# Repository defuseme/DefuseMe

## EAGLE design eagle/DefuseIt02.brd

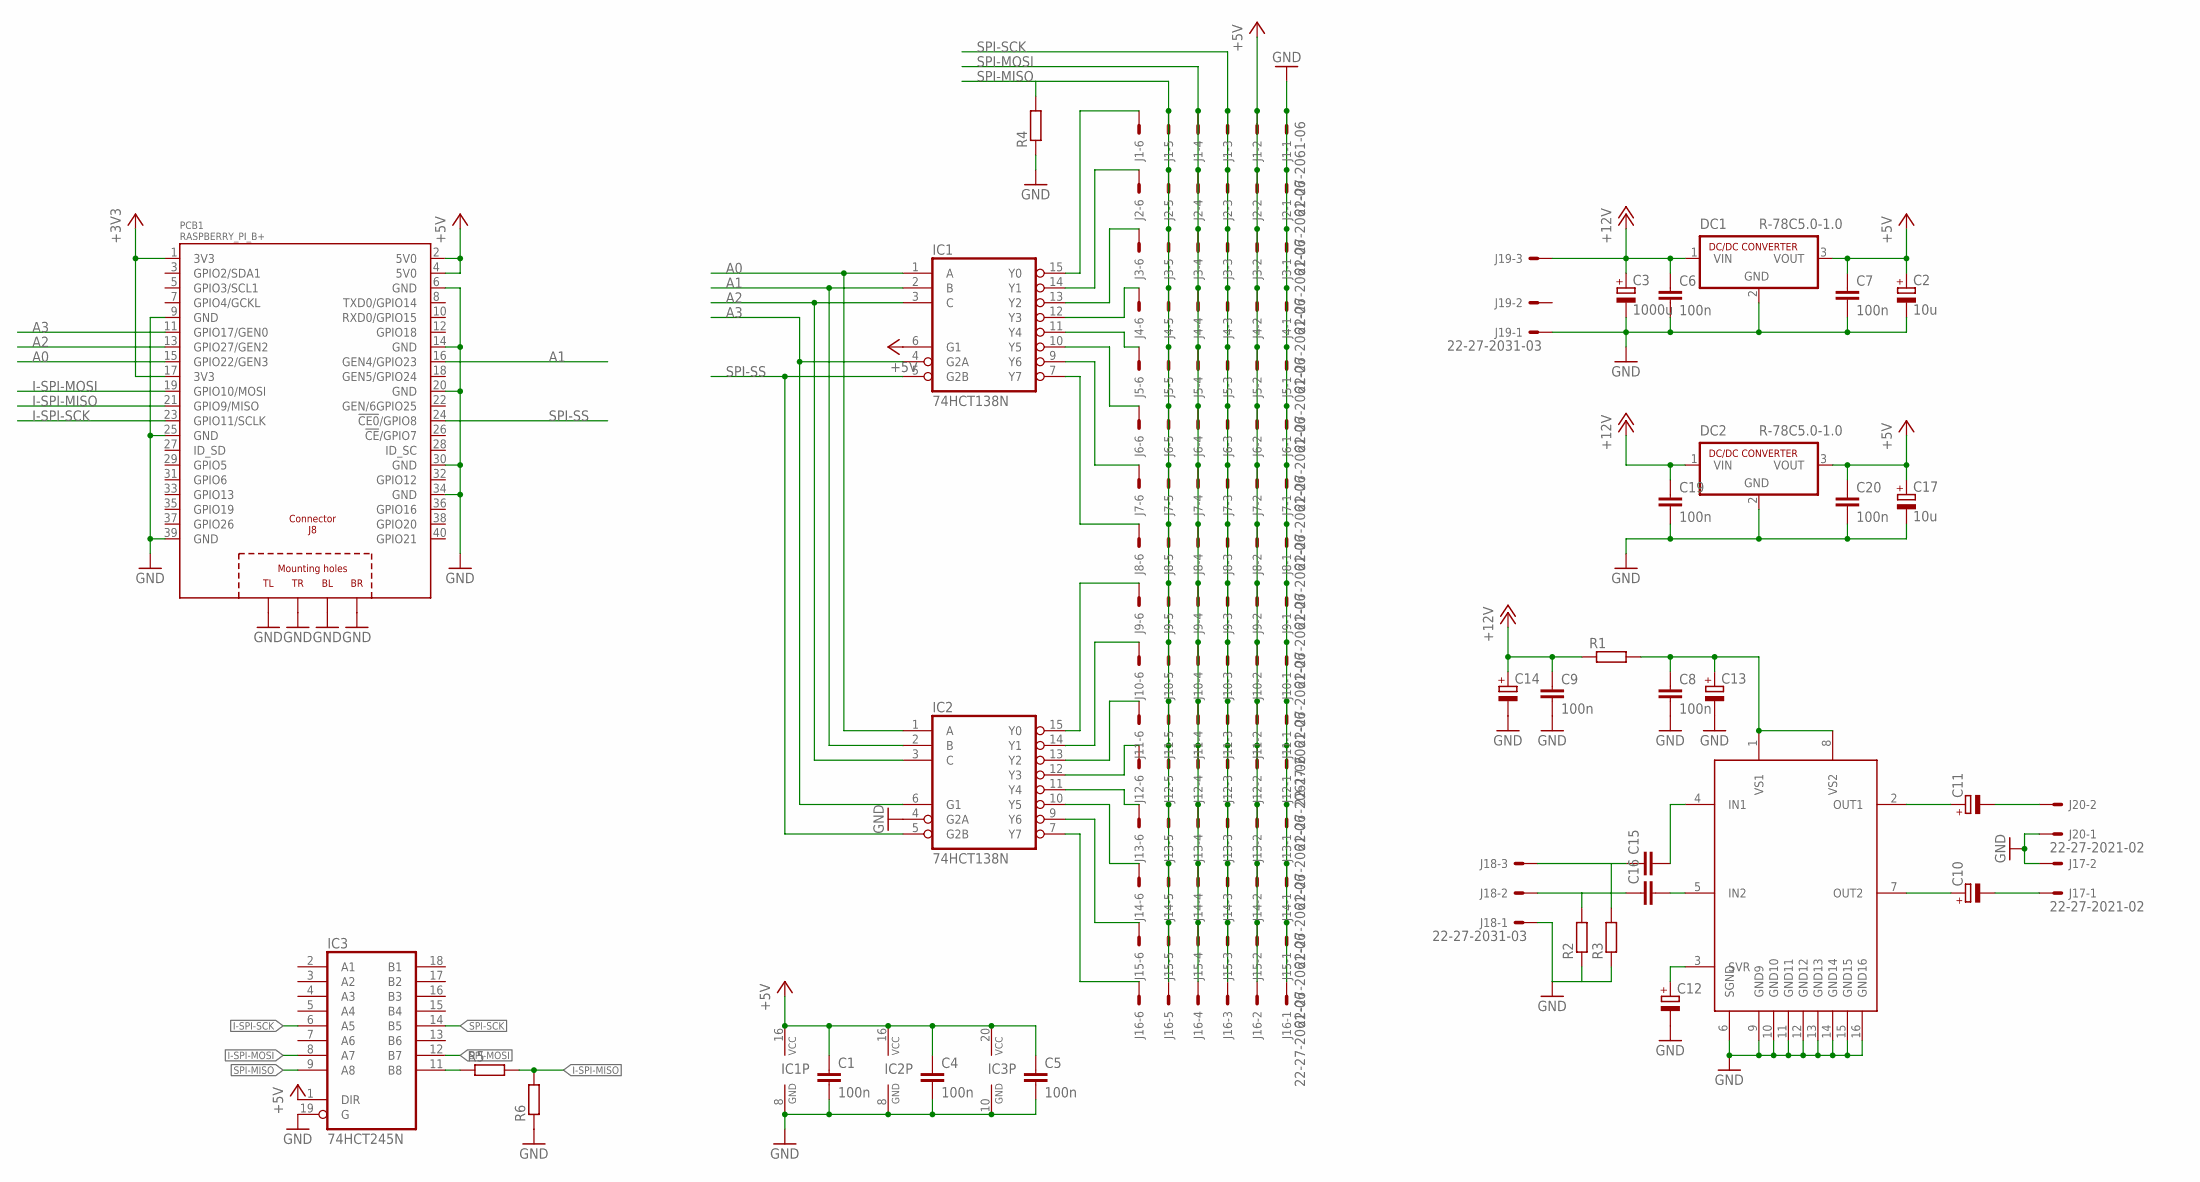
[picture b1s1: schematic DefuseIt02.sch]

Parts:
C1, C4, C5, C6, C7, C8, C9, C19, C20: 100n; C025-025X050
C2, C17: 10u; E3,5-8
C3: 1000u; E7,5-16
C10, C11: CPOL-EUE3.5-8; E3,5-8
C12, C13, C14: CPOL-EUE2.5-5; E2,5-5
C15, C16: C-EU050-030X075; C050-030X075
DC1, DC2: R-78C5.0-1.0; SIP3
IC1, IC2: 74HCT138N; DIL16
IC3: 74HCT245N; DIL20
J1, J2, J3, J4, J5, J6, J7, J8, J9, J10, J11, J12, J13, J14, J15, J16: 22-27-2061-06; 6410-06
J17, J20: 22-27-2021-02; 6410-02
J18, J19: 22-27-2031-03; 6410-03
PCB1: RASPBERRY_PI_B+
R1, R2, R3, R4, R5, R6: R-EU_0207/10; 0207/10
U$1: TDA7268; DIL16

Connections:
+3V3: PCB1.1 (3V3), PCB1.17 (3V3)
+5V: C1.1, C2.+, C4.1, C5.1, C7.1, DC1.3 (VOUT), IC1.6 (G1), IC1.16 (VCC), IC2.16 (VCC), IC3.1 (DIR), IC3.20 (VCC), J1.2, J2.2, J3.2, J4.2, J5.2, J6.2, J7.2, J8.2, J9.2, J10.2, J11.2, J12.2, J13.2, J14.2, J15.2, J16.2
+5VRPI: C17.+, C20.1, DC2.3 (VOUT), PCB1.2 (5V0), PCB1.4 (5V0)
+12V: C3.+, C6.1, C9.1, C14.+, C19.1, DC1.1 (VIN), DC2.1 (VIN), J19.3, R1.1
A0: IC1.1 (A), IC2.1 (A), PCB1.15 (GPIO22/GEN3)
A1: IC1.2 (B), IC2.2 (B), PCB1.16 (GEN4/GPIO23)
A2: IC1.3 (C), IC2.3 (C), PCB1.13 (GPIO27/GEN2)
A3: IC1.4 (G2A), IC2.6 (G1), PCB1.11 (GPIO17/GEN0)
GND: C1.2, C2.-, C3.-, C4.2, C5.2, C6.2, C7.2, C8.2, C9.2, C12.-, C13.-, C14.-, C17.-, C19.2, C20.2, DC1.2 (GND), DC2.2 (GND), IC1.8 (GND), IC2.4 (G2A), IC2.8 (GND), IC3.10 (GND), IC3.19 (G), J1.1, J2.1, J3.1, J4.1, J5.1, J6.1, J7.1, J8.1, J9.1, J10.1, J11.1, J12.1, J13.1, J14.1, J15.1, J16.1, J17.2, J18.1, J19.1, J20.1, PCB1.6 (GND), PCB1.9 (GND), PCB1.14 (GND), PCB1.20 (GND), PCB1.25 (GND), PCB1.30 (GND), PCB1.34 (GND), PCB1.39 (GND), PCB1.PE_BL (BL), PCB1.PE_BR (BR), PCB1.PE_TL (TL), PCB1.PE_TR (TR), R2.1, R3.1, R4.1, R6.1, U$1.6 (SGND), U$1.9 (GND9), U$1.10 (GND10), U$1.11 (GND11), U$1.12 (GND12), U$1.13 (GND13), U$1.14 (GND14), U$1.15 (GND15), U$1.16 (GND16)
I-SPI-MISO: PCB1.21 (GPIO9/MISO), R5.2, R6.2
I-SPI-MOSI: IC3.8 (A7), PCB1.19 (GPIO10/MOSI)
I-SPI-SCK: IC3.6 (A5), PCB1.23 (GPIO11/SCLK)
unnamed: IC1.12 (Y3), J4.6
unnamed: IC1.11 (Y4), J5.6
unnamed: IC1.13 (Y2), J3.6
unnamed: IC1.14 (Y1), J2.6
unnamed: IC1.15 (Y0), J1.6
unnamed: IC1.10 (Y5), J6.6
unnamed: IC1.9 (Y6), J7.6
unnamed: IC1.7 (Y7), J8.6
unnamed: IC2.12 (Y3), J12.6
unnamed: IC2.11 (Y4), J13.6
unnamed: IC2.13 (Y2), J11.6
unnamed: IC2.14 (Y1), J10.6
unnamed: IC2.15 (Y0), J9.6
unnamed: IC2.10 (Y5), J14.6
unnamed: IC2.9 (Y6), J15.6
unnamed: IC2.7 (Y7), J16.6
unnamed: C16.2, U$1.5 (IN2)
unnamed: C12.+, U$1.3 (SVR)
unnamed: C10.+, U$1.7 (OUT2)
unnamed: C11.+, U$1.2 (OUT1)
unnamed: C11.-, J20.2
unnamed: C10.-, J17.1
unnamed: C8.1, C13.+, R1.2, U$1.1 (VS1), U$1.8 (VS2)
unnamed: IC3.11 (B8), R5.1
unnamed: C15.2, U$1.4 (IN1)
unnamed: C16.1, J18.2, R2.2
unnamed: C15.1, J18.3, R3.2
SPI-MISO: IC3.9 (A8), J1.5, J2.5, J3.5, J4.5, J5.5, J6.5, J7.5, J8.5, J9.5, J10.5, J11.5, J12.5, J13.5, J14.5, J15.5, J16.5, R4.2
SPI-MOSI: IC3.12 (B7), J1.4, J2.4, J3.4, J4.4, J5.4, J6.4, J7.4, J8.4, J9.4, J10.4, J11.4, J12.4, J13.4, J14.4, J15.4, J16.4
SPI-SCK: IC3.14 (B5), J1.3, J2.3, J3.3, J4.3, J5.3, J6.3, J7.3, J8.3, J9.3, J10.3, J11.3, J12.3, J13.3, J14.3, J15.3, J16.3
SPI-SS: IC1.5 (G2B), IC2.5 (G2B), PCB1.24 (!CE0!/GPIO8)

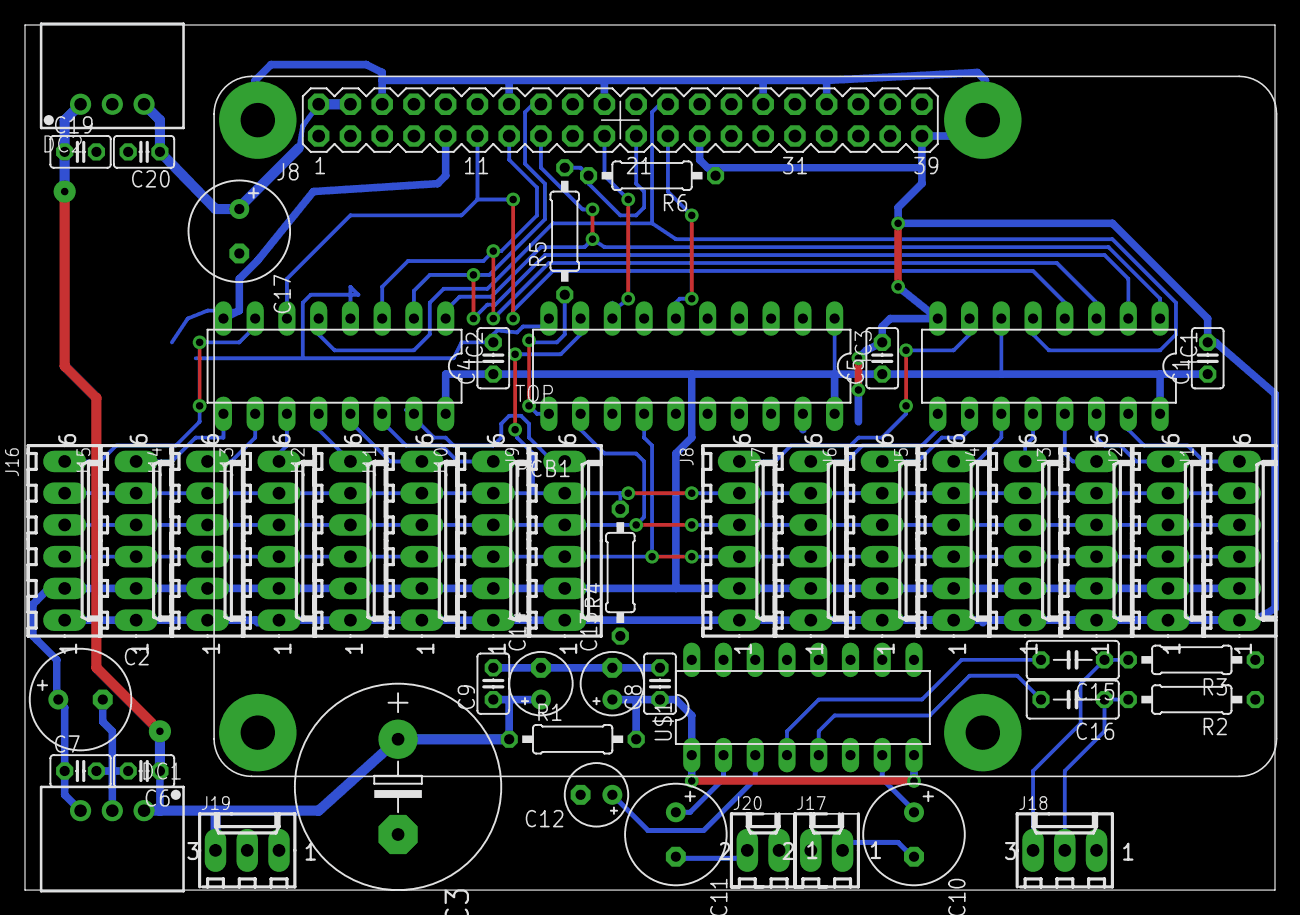
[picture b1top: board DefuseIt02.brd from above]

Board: 2 copper layers, 100.0 x 69.2 mm, 52 parts (0 on the bottom side), 43 nets.

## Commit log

2015-12-09 added eagle subfolder
2015-12-10 Finished first layout w/o audio
2015-12-20 added audio chip; layout correction
2015-12-30 Added function stubs
2016-01-01 Added python master module code project
2016-01-01 Added protocoll command codes
2016-01-01 Prepared test cases and protocoll encoder
2016-09-03 Added protocol description Added .gitignore with *.swp
2016-09-04 MRMCD Overall Commit
2016-10-28 Added LOOPBACK Several minor tweaks Still no full function....
2016-11-05 First contact to a new world (arduino) via SPI
2016-11-05 Added to SPI dedicated test files
2016-12-15 Added first draft of module lib and samples
2016-12-15 Added draft of module doc
2016-12-18 work release
2016-12-18 Added Brief layout for development
2016-12-18 New examples from Pföt
2016-12-19 added serial number generator and printer
2016-12-19 Finished firmware and paper inlays
2016-12-19 fixed demo mode
2016-12-19 Added Main Display firmware
2016-12-21 Added docs
2016-12-21 Added module BigSwitch4Lamps
2016-12-21 case sensitive names
2016-12-21 seed works now/ demo mode starts on MISO not connected/ bug fixes...
2016-12-21 updated modules to new library functions etc
2016-12-21 documented "REGISTER"
2016-12-21 added REGISTER field, added status, added access by slot
2016-12-21 a lot of changes: game works now ;)
2016-12-21 added utils (for do_every function)
2016-12-22 documentation and beautify
2016-12-22 Improved doc
2016-12-23 fixed flow chart bug - rework doc
2016-12-23 add airplaine module description
2016-12-23 rename modulle
2016-12-23 Finished module firmware
2016-12-23 moved MultiSwitch.* to lib
2016-12-23 add devstage code for simon says
2016-12-23 Finished module firmware for BlueBlink22
2016-12-24 Added module Blue Button Stripe - work release
2016-12-24 Last bugfixes Defused status broadcast
2016-12-28 fixed disarm bug
2016-12-28 added flickering to LEDs
2016-12-29 Added some functions
2016-12-30 work release of module lib
2016-12-30 Kind of 'runnable' version from 33c3
2016-12-31 moved module source code 1 folder down
2017-01-02 rework of pin array lib
2017-01-02 documentation / reorg / VS projects
2017-01-03 more scematics
2017-01-04 documentation
2017-01-05 documentation / laser cut files
